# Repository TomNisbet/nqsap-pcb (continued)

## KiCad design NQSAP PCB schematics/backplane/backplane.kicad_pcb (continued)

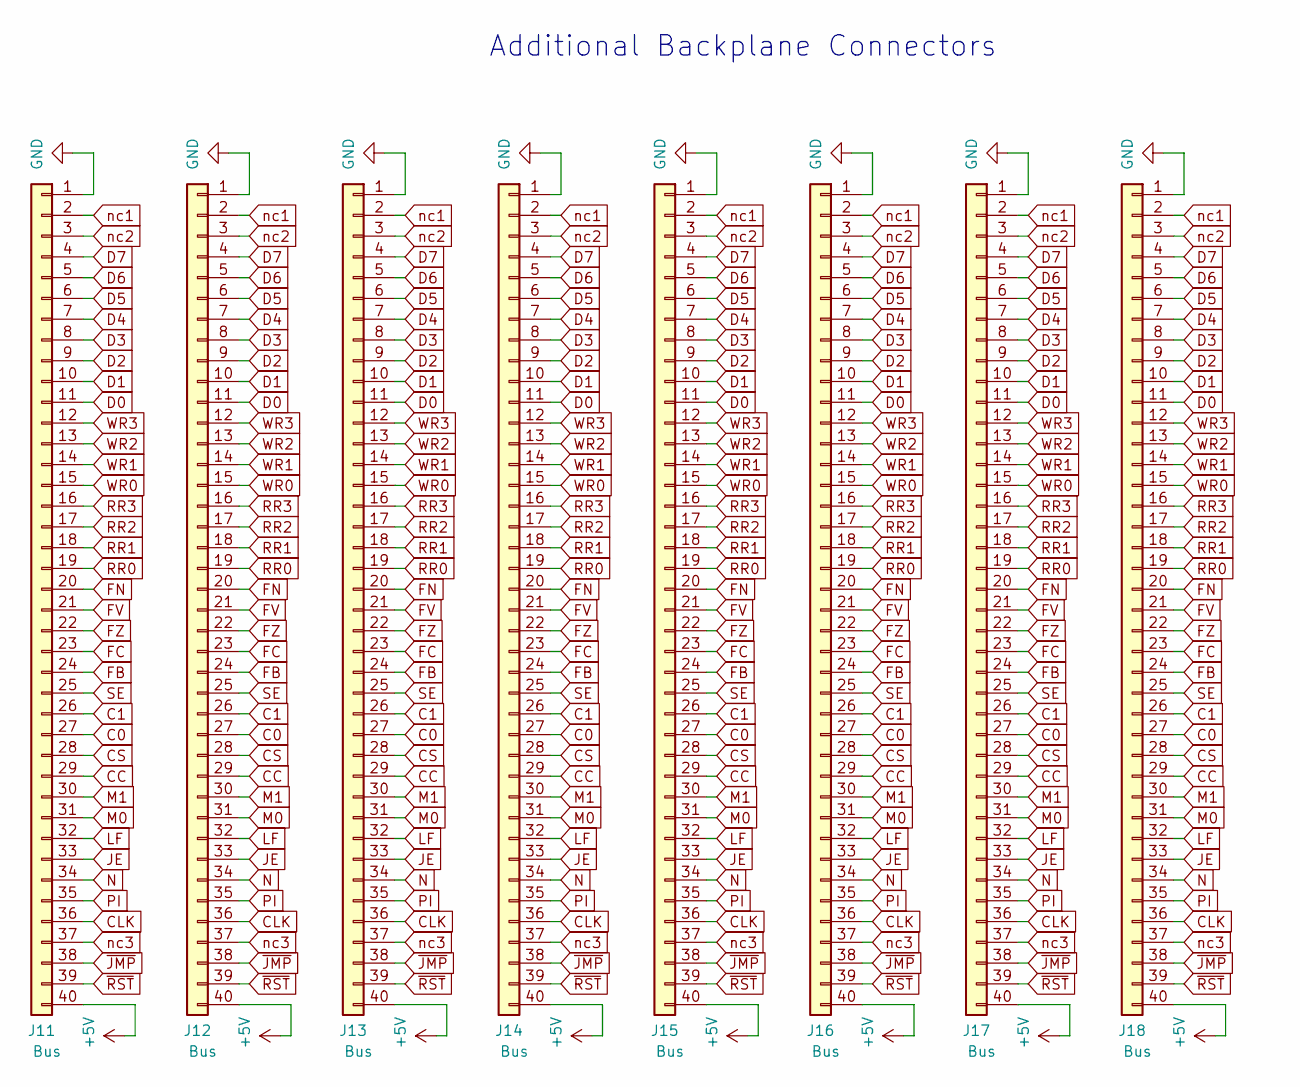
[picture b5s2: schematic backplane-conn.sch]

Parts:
J11, J12, J13, J14, J15, J16, J17, J18: Bus; PinSocket_1x40_P2.54mm_Vertical

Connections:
+5V: J11.40, J12.40, J13.40, J14.40, J15.40, J16.40, J17.40, J18.40; also elsewhere on the board
C0: J11.27, J12.27, J13.27, J14.27, J15.27, J16.27, J17.27, J18.27; also elsewhere on the board
C1: J11.26, J12.26, J13.26, J14.26, J15.26, J16.26, J17.26, J18.26; also elsewhere on the board
CC: J11.29, J12.29, J13.29, J14.29, J15.29, J16.29, J17.29, J18.29; also elsewhere on the board
CLK: J11.36, J12.36, J13.36, J14.36, J15.36, J16.36, J17.36, J18.36; also elsewhere on the board
CS: J11.28, J12.28, J13.28, J14.28, J15.28, J16.28, J17.28, J18.28; also elsewhere on the board
D0: J11.11, J12.11, J13.11, J14.11, J15.11, J16.11, J17.11, J18.11; also elsewhere on the board
D1: J11.10, J12.10, J13.10, J14.10, J15.10, J16.10, J17.10, J18.10; also elsewhere on the board
D2: J11.9, J12.9, J13.9, J14.9, J15.9, J16.9, J17.9, J18.9; also elsewhere on the board
D3: J11.8, J12.8, J13.8, J14.8, J15.8, J16.8, J17.8, J18.8; also elsewhere on the board
D4: J11.7, J12.7, J13.7, J14.7, J15.7, J16.7, J17.7, J18.7; also elsewhere on the board
D5: J11.6, J12.6, J13.6, J14.6, J15.6, J16.6, J17.6, J18.6; also elsewhere on the board
D6: J11.5, J12.5, J13.5, J14.5, J15.5, J16.5, J17.5, J18.5; also elsewhere on the board
D7: J11.4, J12.4, J13.4, J14.4, J15.4, J16.4, J17.4, J18.4; also elsewhere on the board
FB: J11.24, J12.24, J13.24, J14.24, J15.24, J16.24, J17.24, J18.24; also elsewhere on the board
FC: J11.23, J12.23, J13.23, J14.23, J15.23, J16.23, J17.23, J18.23; also elsewhere on the board
FN: J11.20, J12.20, J13.20, J14.20, J15.20, J16.20, J17.20, J18.20; also elsewhere on the board
FV: J11.21, J12.21, J13.21, J14.21, J15.21, J16.21, J17.21, J18.21; also elsewhere on the board
FZ: J11.22, J12.22, J13.22, J14.22, J15.22, J16.22, J17.22, J18.22; also elsewhere on the board
GND: J11.1, J12.1, J13.1, J14.1, J15.1, J16.1, J17.1, J18.1; also elsewhere on the board
JE: J11.33, J12.33, J13.33, J14.33, J15.33, J16.33, J17.33, J18.33; also elsewhere on the board
LF: J11.32, J12.32, J13.32, J14.32, J15.32, J16.32, J17.32, J18.32; also elsewhere on the board
M0: J11.31, J12.31, J13.31, J14.31, J15.31, J16.31, J17.31, J18.31; also elsewhere on the board
M1: J11.30, J12.30, J13.30, J14.30, J15.30, J16.30, J17.30, J18.30; also elsewhere on the board
N: J11.34, J12.34, J13.34, J14.34, J15.34, J16.34, J17.34, J18.34; also elsewhere on the board
PI: J11.35, J12.35, J13.35, J14.35, J15.35, J16.35, J17.35, J18.35; also elsewhere on the board
RR0: J11.19, J12.19, J13.19, J14.19, J15.19, J16.19, J17.19, J18.19; also elsewhere on the board
RR1: J11.18, J12.18, J13.18, J14.18, J15.18, J16.18, J17.18, J18.18; also elsewhere on the board
RR2: J11.17, J12.17, J13.17, J14.17, J15.17, J16.17, J17.17, J18.17; also elsewhere on the board
RR3: J11.16, J12.16, J13.16, J14.16, J15.16, J16.16, J17.16, J18.16; also elsewhere on the board
SE: J11.25, J12.25, J13.25, J14.25, J15.25, J16.25, J17.25, J18.25; also elsewhere on the board
WR0: J11.15, J12.15, J13.15, J14.15, J15.15, J16.15, J17.15, J18.15; also elsewhere on the board
WR1: J11.14, J12.14, J13.14, J14.14, J15.14, J16.14, J17.14, J18.14; also elsewhere on the board
WR2: J11.13, J12.13, J13.13, J14.13, J15.13, J16.13, J17.13, J18.13; also elsewhere on the board
WR3: J11.12, J12.12, J13.12, J14.12, J15.12, J16.12, J17.12, J18.12; also elsewhere on the board
nc1: J11.2, J12.2, J13.2, J14.2, J15.2, J16.2, J17.2, J18.2; also elsewhere on the board
nc2: J11.3, J12.3, J13.3, J14.3, J15.3, J16.3, J17.3, J18.3; also elsewhere on the board
nc3: J11.37, J12.37, J13.37, J14.37, J15.37, J16.37, J17.37, J18.37; also elsewhere on the board
~JMP: J11.38, J12.38, J13.38, J14.38, J15.38, J16.38, J17.38, J18.38; also elsewhere on the board
~RST: J11.39, J12.39, J13.39, J14.39, J15.39, J16.39, J17.39, J18.39; also elsewhere on the board

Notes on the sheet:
Additional Backplane Connectors

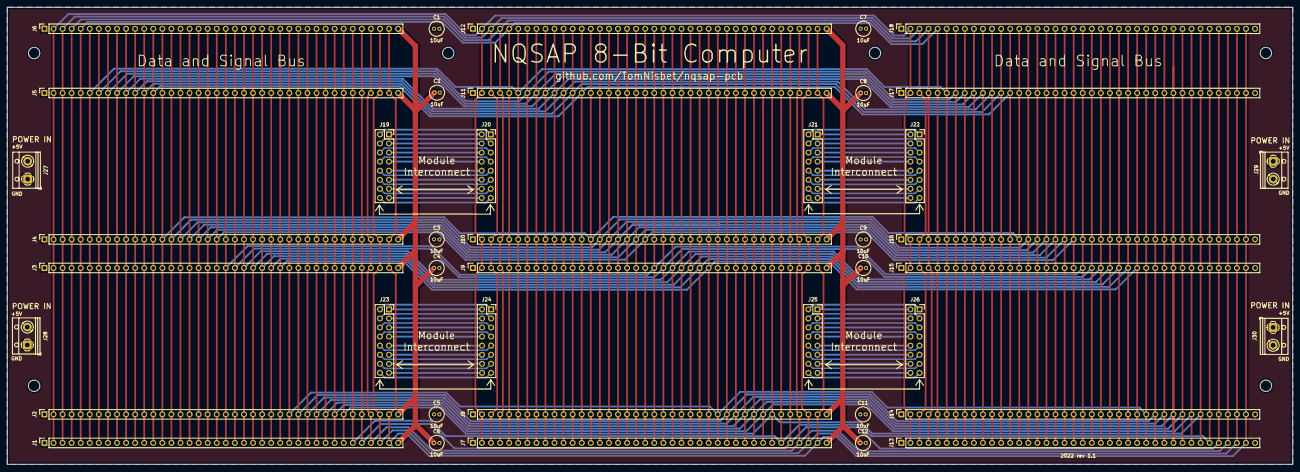
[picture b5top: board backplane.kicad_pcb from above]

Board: 2 copper layers, 360.0 x 128.0 mm, 42 parts (0 on the bottom side), 104 nets.

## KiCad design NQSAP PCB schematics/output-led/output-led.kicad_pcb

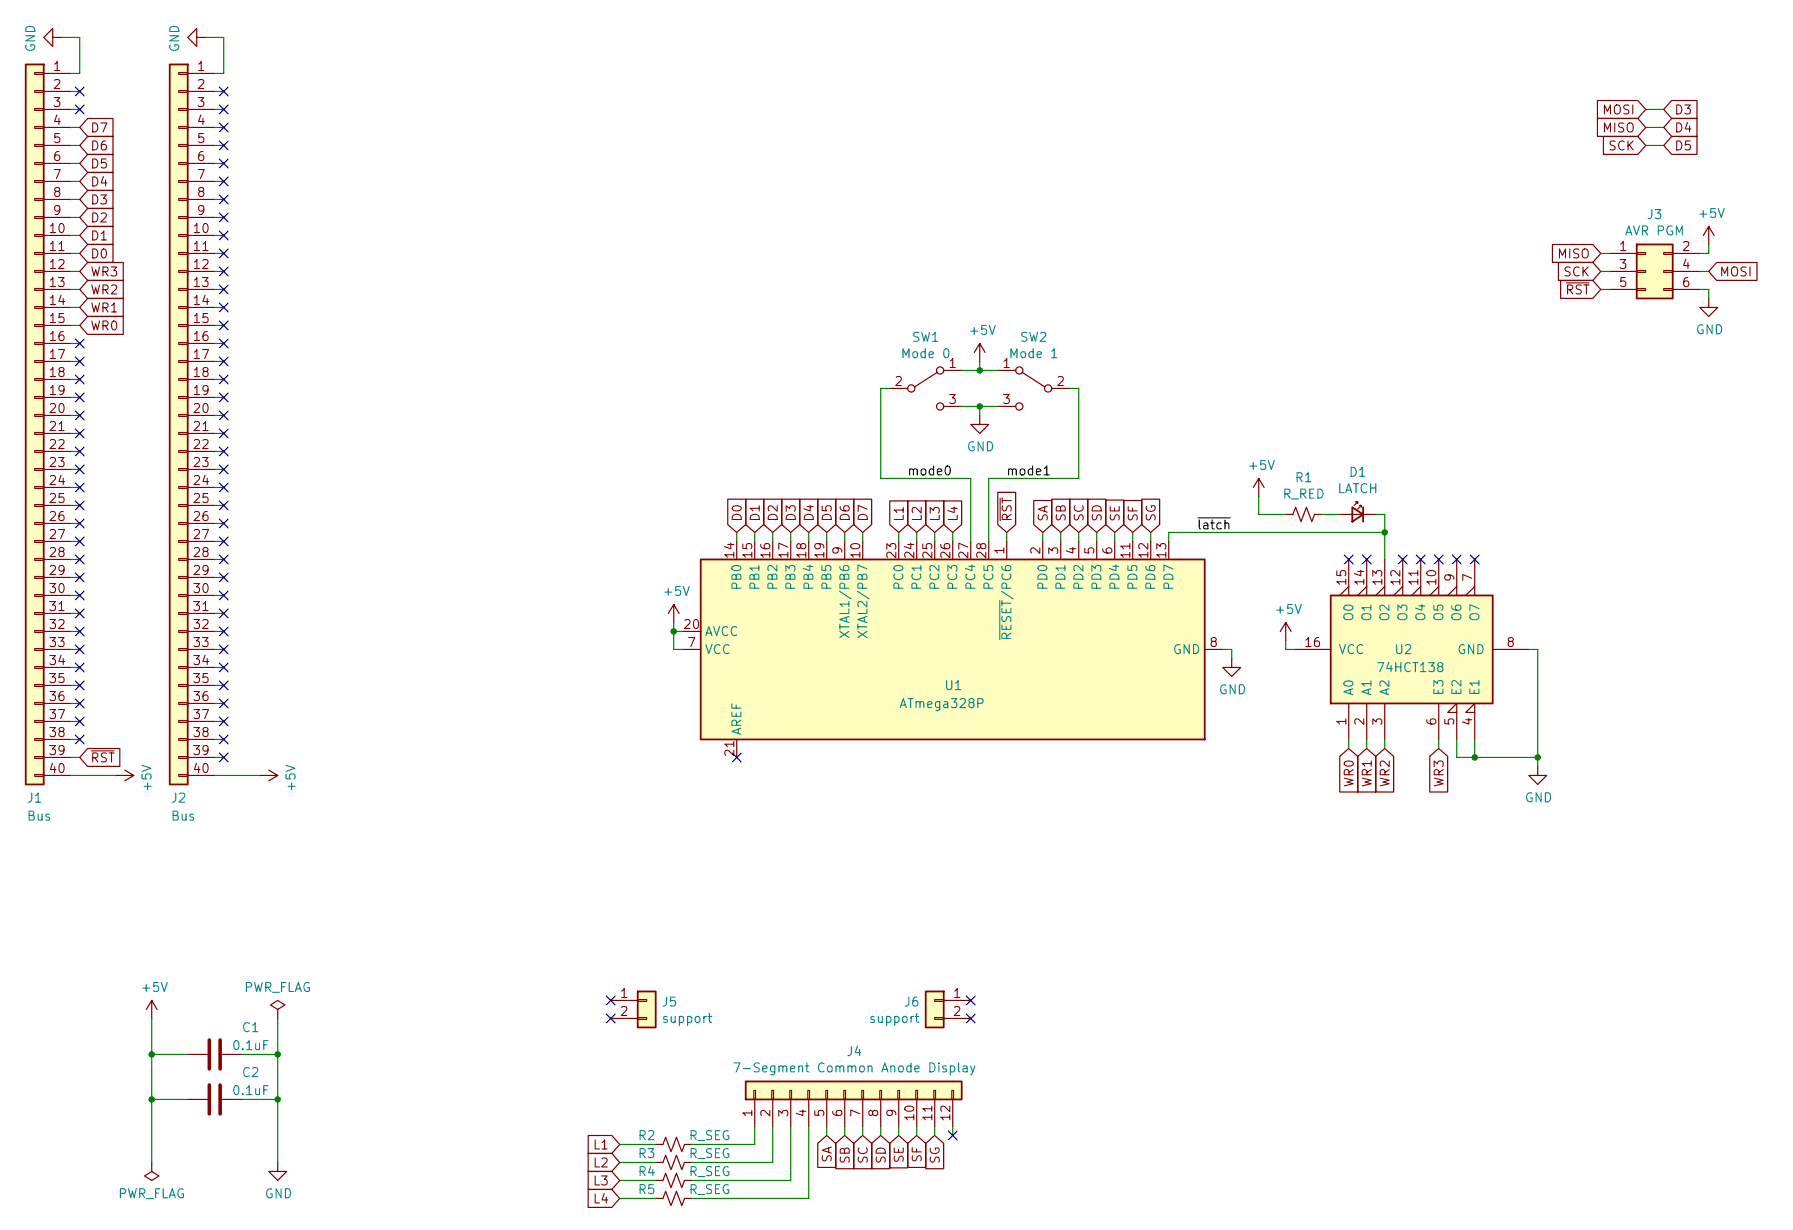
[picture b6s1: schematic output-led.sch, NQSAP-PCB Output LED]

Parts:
C1, C2: 0.1uF; C_0805_2012Metric_Pad1.18x1.45mm_HandSolder
D1: LATCH; LED_0805_2012Metric_Pad1.15x1.40mm_HandSolder
J1, J2: Bus; PinHeader_1x40_P2.54mm_Vertical
J3: AVR PGM; PinHeader_2x03_P2.54mm_Vertical
J4: 7-Segment Common Anode Display; PinSocket_1x12_P2.54mm_Vertical
J5, J6: support; PinSocket_1x02_P2.54mm_Vertical
R1: R_RED; R_0805_2012Metric_Pad1.20x1.40mm_HandSolder
R2, R3, R4, R5: R_SEG; R_0805_2012Metric_Pad1.20x1.40mm_HandSolder
SW1: Mode 0; Switch_Slide_11.6x4mm_EG1218
SW2: Mode 1; Switch_Slide_11.6x4mm_EG1218
U1: ATmega328P; DIP-28_W7.62mm
U2: 74HCT138; DIP-16_W7.62mm

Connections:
+5V: C1.2, C2.2, J1.40, J2.40, J3.2, R1.2, SW1.1 (A), SW2.1 (A), U1.7 (VCC), U1.20 (AVCC), U2.16 (VCC)
/mode0: SW1.2 (B), U1.27 (PC4)
/mode1: SW2.2 (B), U1.28 (PC5)
/~latch: D1.1 (K), U1.13 (PD7), U2.13 (O2)
D0: J1.11, U1.14 (PB0)
D1: J1.10, U1.15 (PB1)
D2: J1.9, U1.16 (PB2)
D3: J1.8, J3.4, U1.17 (PB3)
D4: J1.7, J3.1, U1.18 (PB4)
D5: J1.6, J3.3, U1.19 (PB5)
D6: J1.5, U1.9 (XTAL1/PB6)
D7: J1.4, U1.10 (XTAL2/PB7)
GND: C1.1, C2.1, J1.1, J2.1, J3.6, SW1.3 (C), SW2.3 (C), U1.8 (GND), U1.22 (GND), U2.4 (E1), U2.5 (E2), U2.8 (GND)
L1: R2.2, U1.23 (PC0)
L2: R3.2, U1.24 (PC1)
L3: R4.2, U1.25 (PC2)
L4: R5.2, U1.26 (PC3)
unnamed: D1.2 (A), R1.1
unnamed: J4.1, R2.1
unnamed: J4.2, R3.1
unnamed: J4.3, R4.1
unnamed: J4.4, R5.1
SA: J4.5, U1.2 (PD0)
SB: J4.6, U1.3 (PD1)
SC: J4.7, U1.4 (PD2)
SD: J4.8, U1.5 (PD3)
SE: J4.9, U1.6 (PD4)
SF: J4.10, U1.11 (PD5)
SG: J4.11, U1.12 (PD6)
WR0: J1.15, U2.1 (A0)
WR1: J1.14, U2.2 (A1)
WR2: J1.13, U2.3 (A2)
WR3: J1.12, U2.6 (E3)
~RST: J1.39, J3.5, U1.1 (~RESET~/PC6)

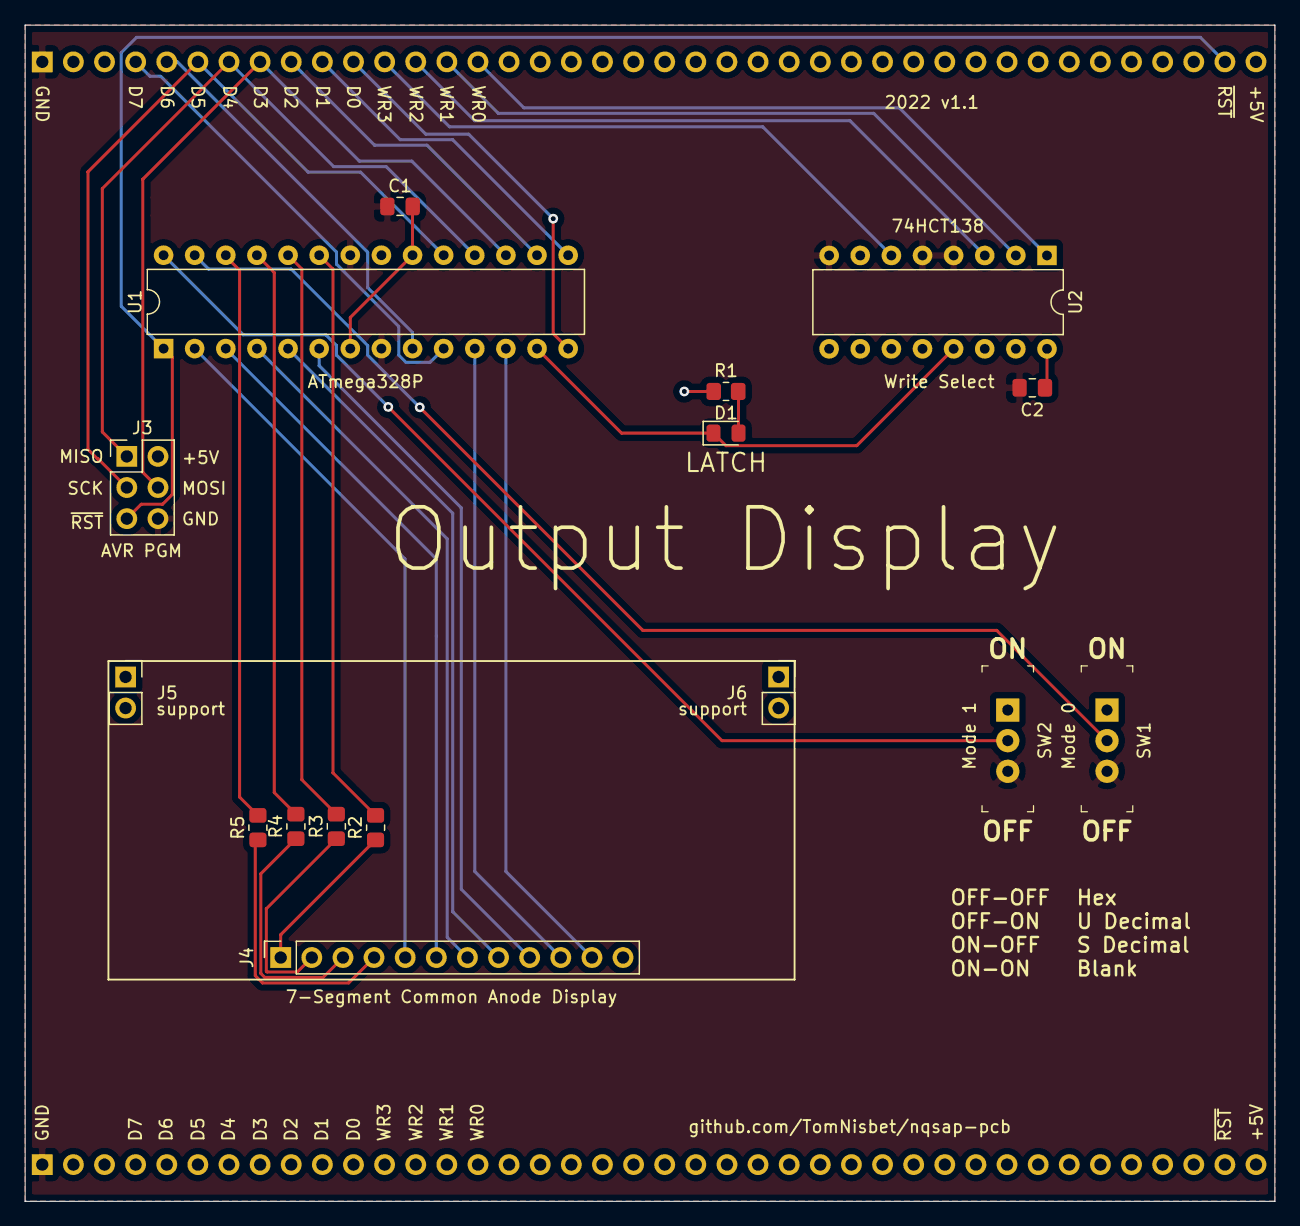
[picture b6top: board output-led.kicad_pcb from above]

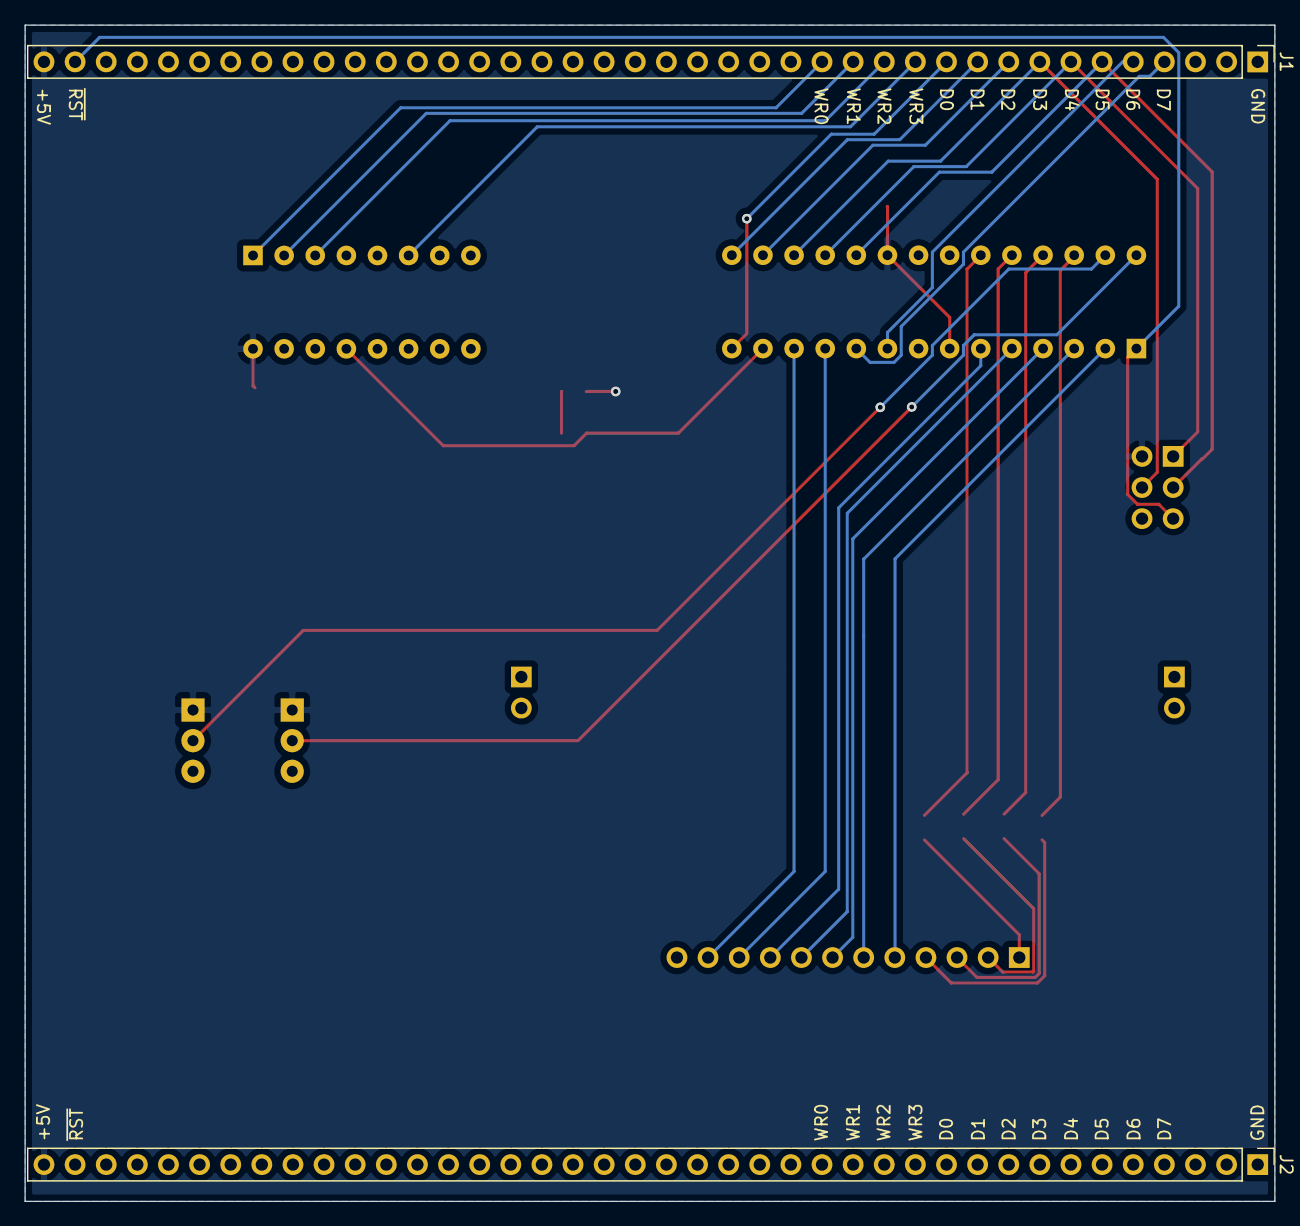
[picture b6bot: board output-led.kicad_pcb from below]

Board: 2 copper layers, 102.0 x 96.0 mm, 18 parts (2 on the bottom side), 34 nets.

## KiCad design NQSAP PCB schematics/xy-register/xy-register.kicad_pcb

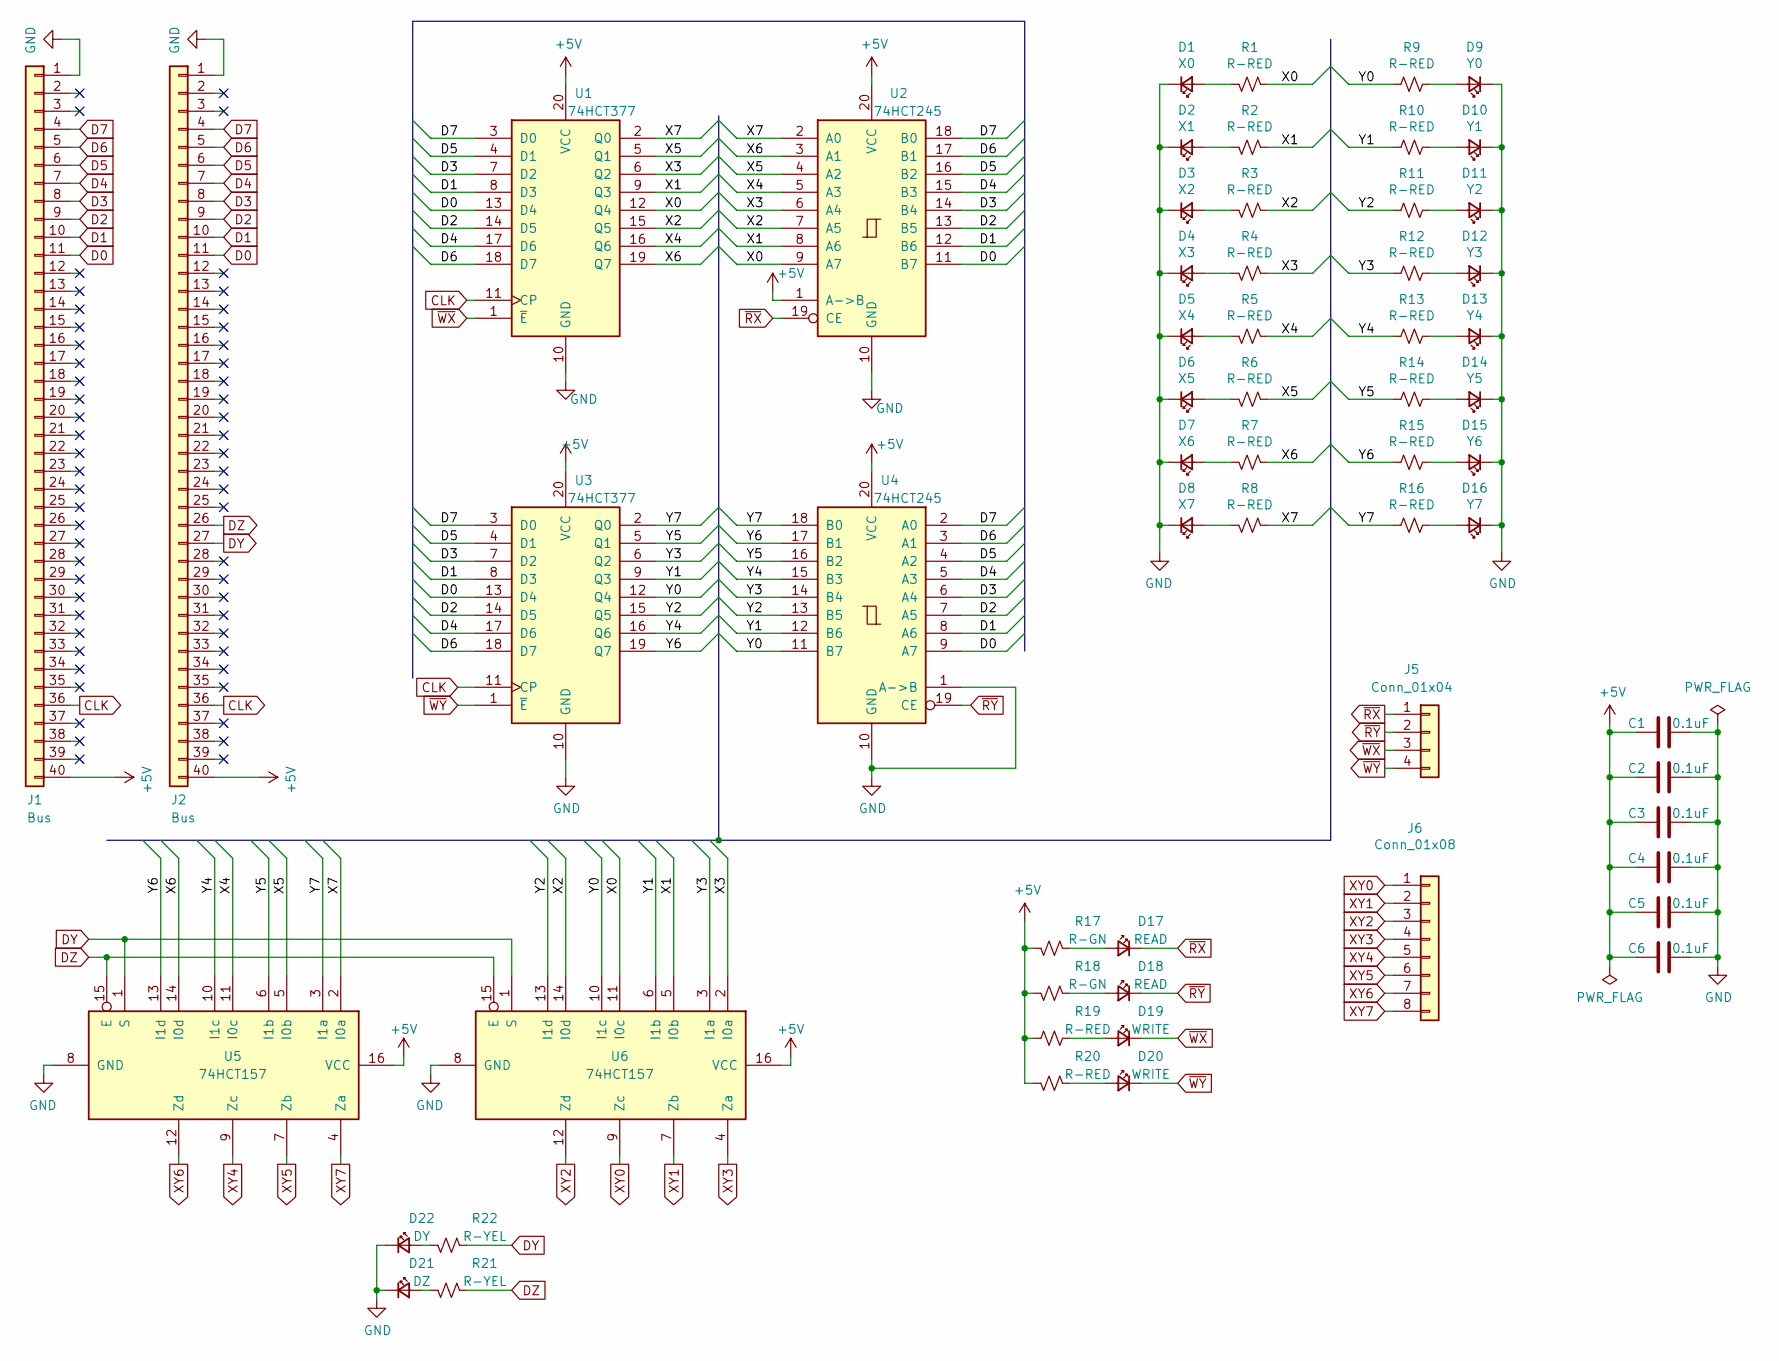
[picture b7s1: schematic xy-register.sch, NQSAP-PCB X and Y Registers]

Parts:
C1, C2, C3, C4, C5, C6: 0.1uF; C_0805_2012Metric_Pad1.18x1.45mm_HandSolder
D1: X0; LED_0805_2012Metric_Pad1.15x1.40mm_HandSolder
D2: X1; LED_0805_2012Metric_Pad1.15x1.40mm_HandSolder
D3: X2; LED_0805_2012Metric_Pad1.15x1.40mm_HandSolder
D4: X3; LED_0805_2012Metric_Pad1.15x1.40mm_HandSolder
D5: X4; LED_0805_2012Metric_Pad1.15x1.40mm_HandSolder
D6: X5; LED_0805_2012Metric_Pad1.15x1.40mm_HandSolder
D7: X6; LED_0805_2012Metric_Pad1.15x1.40mm_HandSolder
D8: X7; LED_0805_2012Metric_Pad1.15x1.40mm_HandSolder
D9: Y0; LED_0805_2012Metric_Pad1.15x1.40mm_HandSolder
D10: Y1; LED_0805_2012Metric_Pad1.15x1.40mm_HandSolder
D11: Y2; LED_0805_2012Metric_Pad1.15x1.40mm_HandSolder
D12: Y3; LED_0805_2012Metric_Pad1.15x1.40mm_HandSolder
D13: Y4; LED_0805_2012Metric_Pad1.15x1.40mm_HandSolder
D14: Y5; LED_0805_2012Metric_Pad1.15x1.40mm_HandSolder
D15: Y6; LED_0805_2012Metric_Pad1.15x1.40mm_HandSolder
D16: Y7; LED_0805_2012Metric_Pad1.15x1.40mm_HandSolder
D17, D18: READ; LED_0805_2012Metric_Pad1.15x1.40mm_HandSolder
D19, D20: WRITE; LED_0805_2012Metric_Pad1.15x1.40mm_HandSolder
D21: DZ; LED_0805_2012Metric_Pad1.15x1.40mm_HandSolder
D22: DY; LED_0805_2012Metric_Pad1.15x1.40mm_HandSolder
J1, J2: Bus; PinHeader_1x40_P2.54mm_Vertical
J5: Conn_01x04; PinHeader_1x04_P2.54mm_Vertical
J6: Conn_01x08; PinHeader_1x08_P2.54mm_Vertical
R1, R2, R3, R4, R5, R6, R7, R8, R9, R10, R11, R12, R13, R14, R15, R16, R19, R20: R-RED; R_0805_2012Metric_Pad1.20x1.40mm_HandSolder
R17, R18: R-GN; R_0805_2012Metric_Pad1.20x1.40mm_HandSolder
R21, R22: R-YEL; R_0805_2012Metric_Pad1.20x1.40mm_HandSolder
U1, U3: 74HCT377; DIP-20_W7.62mm
U2, U4: 74HCT245; DIP-20_W7.62mm
U5, U6: 74HCT157; DIP-16_W7.62mm

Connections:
+5V: C1.2, C2.2, C3.2, C4.2, C5.2, C6.2, J1.40, J2.40, R17.1, R18.1, R19.2, R20.1, U1.20 (VCC), U2.1 (A->B), U2.20 (VCC), U3.20 (VCC), U4.20 (VCC), U5.16 (VCC), U6.16 (VCC)
/X0: R1.2, U1.12 (Q4), U2.9 (A7), U6.11 (I0c)
/X1: R2.2, U1.9 (Q3), U2.8 (A6), U6.5 (I0b)
/X2: R3.2, U1.15 (Q5), U2.7 (A5), U6.14 (I0d)
/X3: R4.2, U1.6 (Q2), U2.6 (A4), U6.2 (I0a)
/X4: R5.2, U1.16 (Q6), U2.5 (A3), U5.11 (I0c)
/X5: R6.2, U1.5 (Q1), U2.4 (A2), U5.5 (I0b)
/X6: R7.2, U1.19 (Q7), U2.3 (A1), U5.14 (I0d)
/X7: R8.2, U1.2 (Q0), U2.2 (A0), U5.2 (I0a)
/Y0: R9.2, U3.12 (Q4), U4.11 (B7), U6.10 (I1c)
/Y1: R10.2, U3.9 (Q3), U4.12 (B6), U6.6 (I1b)
/Y2: R11.2, U3.15 (Q5), U4.13 (B5), U6.13 (I1d)
/Y3: R12.2, U3.6 (Q2), U4.14 (B4), U6.3 (I1a)
/Y4: R13.2, U3.16 (Q6), U4.15 (B3), U5.10 (I1c)
/Y5: R14.2, U3.5 (Q1), U4.16 (B2), U5.6 (I1b)
/Y6: R15.2, U3.19 (Q7), U4.17 (B1), U5.13 (I1d)
/Y7: R16.2, U3.2 (Q0), U4.18 (B0), U5.3 (I1a)
CLK: J1.36, J2.36, U1.11 (CP), U3.11 (CP)
D0: J1.11, J2.11, U1.13 (D4), U2.11 (B7), U3.13 (D4), U4.9 (A7)
D1: J1.10, J2.10, U1.8 (D3), U2.12 (B6), U3.8 (D3), U4.8 (A6)
D2: J1.9, J2.9, U1.14 (D5), U2.13 (B5), U3.14 (D5), U4.7 (A5)
D3: J1.8, J2.8, U1.7 (D2), U2.14 (B4), U3.7 (D2), U4.6 (A4)
D4: J1.7, J2.7, U1.17 (D6), U2.15 (B3), U3.17 (D6), U4.5 (A3)
D5: J1.6, J2.6, U1.4 (D1), U2.16 (B2), U3.4 (D1), U4.4 (A2)
D6: J1.5, J2.5, U1.18 (D7), U2.17 (B1), U3.18 (D7), U4.3 (A1)
D7: J1.4, J2.4, U1.3 (D0), U2.18 (B0), U3.3 (D0), U4.2 (A0)
DY: J2.27, R22.2, U5.1 (S), U6.1 (S)
DZ: J2.26, R21.2, U5.15 (E), U6.15 (E)
GND: C1.1, C2.1, C3.1, C4.1, C5.1, C6.1, D1.1 (K), D2.1 (K), D3.1 (K), D4.1 (K), D5.1 (K), D6.1 (K), D7.1 (K), D8.1 (K), D9.1 (K), D10.1 (K), D11.1 (K), D12.1 (K), D13.1 (K), D14.1 (K), D15.1 (K), D16.1 (K), D21.1 (K), D22.1 (K), J1.1, J2.1, U1.10 (GND), U2.10 (GND), U3.10 (GND), U4.1 (A->B), U4.10 (GND), U5.8 (GND), U6.8 (GND)
unnamed: D1.2 (A), R1.1
unnamed: D2.2 (A), R2.1
unnamed: D3.2 (A), R3.1
unnamed: D4.2 (A), R4.1
unnamed: D5.2 (A), R5.1
unnamed: D6.2 (A), R6.1
unnamed: D7.2 (A), R7.1
unnamed: D8.2 (A), R8.1
unnamed: D9.2 (A), R9.1
unnamed: D10.2 (A), R10.1
unnamed: D11.2 (A), R11.1
unnamed: D12.2 (A), R12.1
unnamed: D13.2 (A), R13.1
unnamed: D14.2 (A), R14.1
unnamed: D15.2 (A), R15.1
unnamed: D16.2 (A), R16.1
unnamed: D17.2 (A), R17.2
unnamed: D18.2 (A), R18.2
unnamed: D19.2 (A), R19.1
unnamed: D20.2 (A), R20.2
unnamed: D21.2 (A), R21.1
unnamed: D22.2 (A), R22.1
XY0: J6.1, U6.9 (Zc)
XY1: J6.2, U6.7 (Zb)
XY2: J6.3, U6.12 (Zd)
XY3: J6.4, U6.4 (Za)
XY4: J6.5, U5.9 (Zc)
XY5: J6.6, U5.7 (Zb)
XY6: J6.7, U5.12 (Zd)
XY7: J6.8, U5.4 (Za)
~RX: D17.1 (K), J5.1, U2.19 (CE)
~RY: D18.1 (K), J5.2, U4.19 (CE)
~WX: D19.1 (K), J5.3, U1.1 (~E)
~WY: D20.1 (K), J5.4, U3.1 (~E)

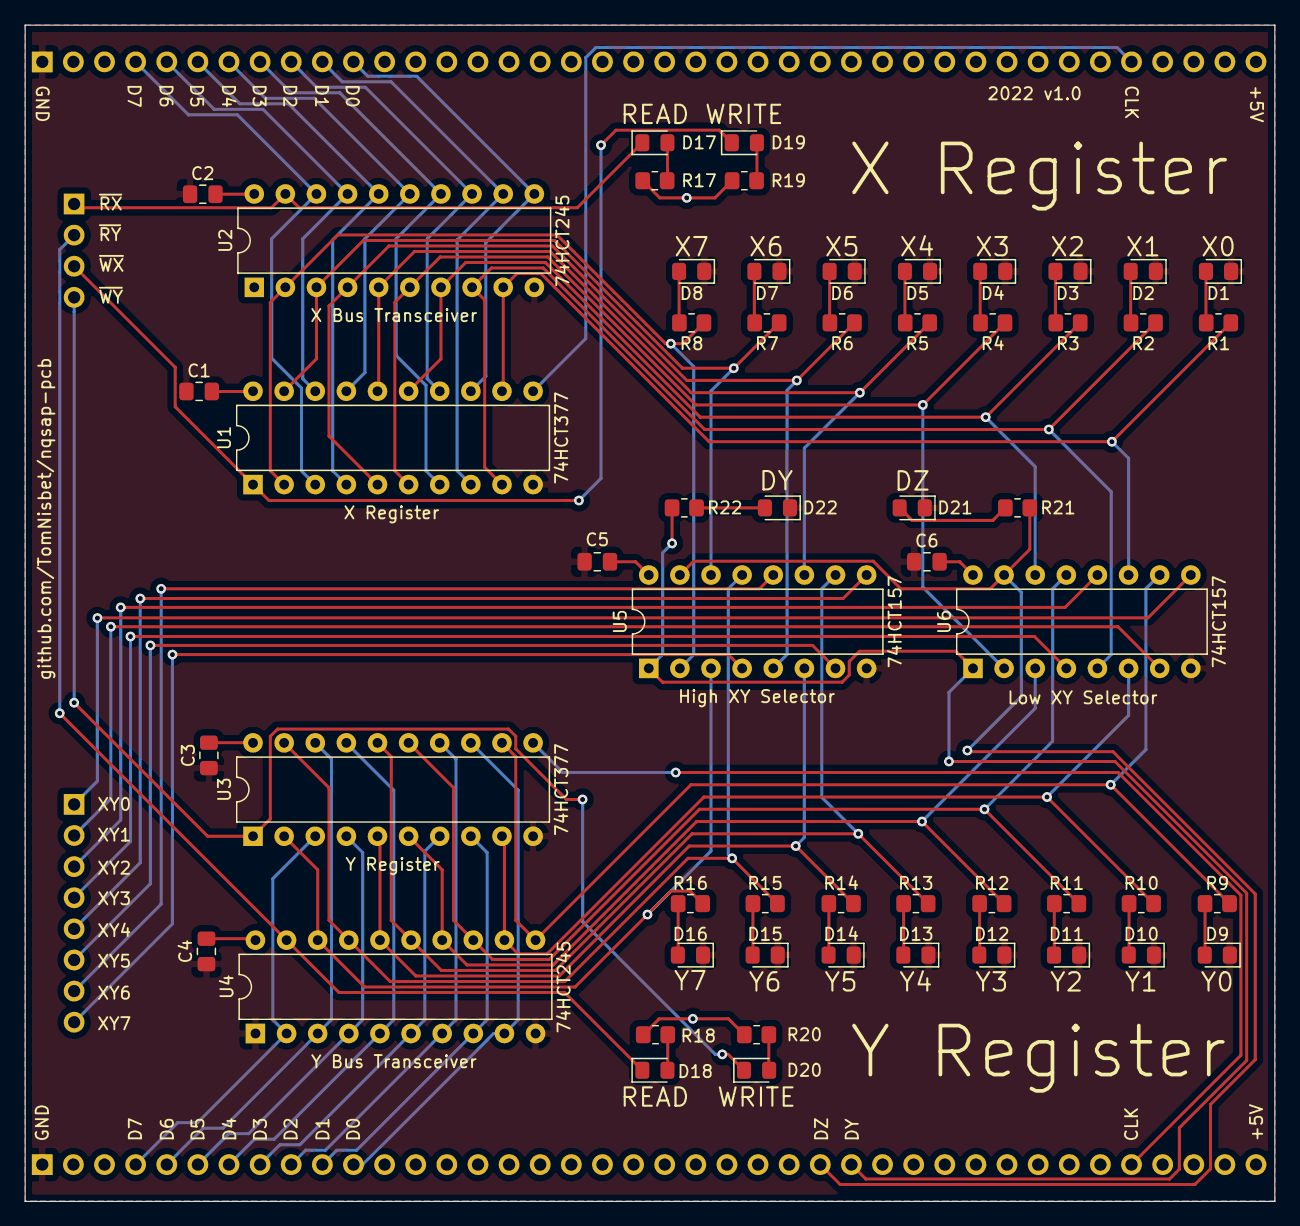
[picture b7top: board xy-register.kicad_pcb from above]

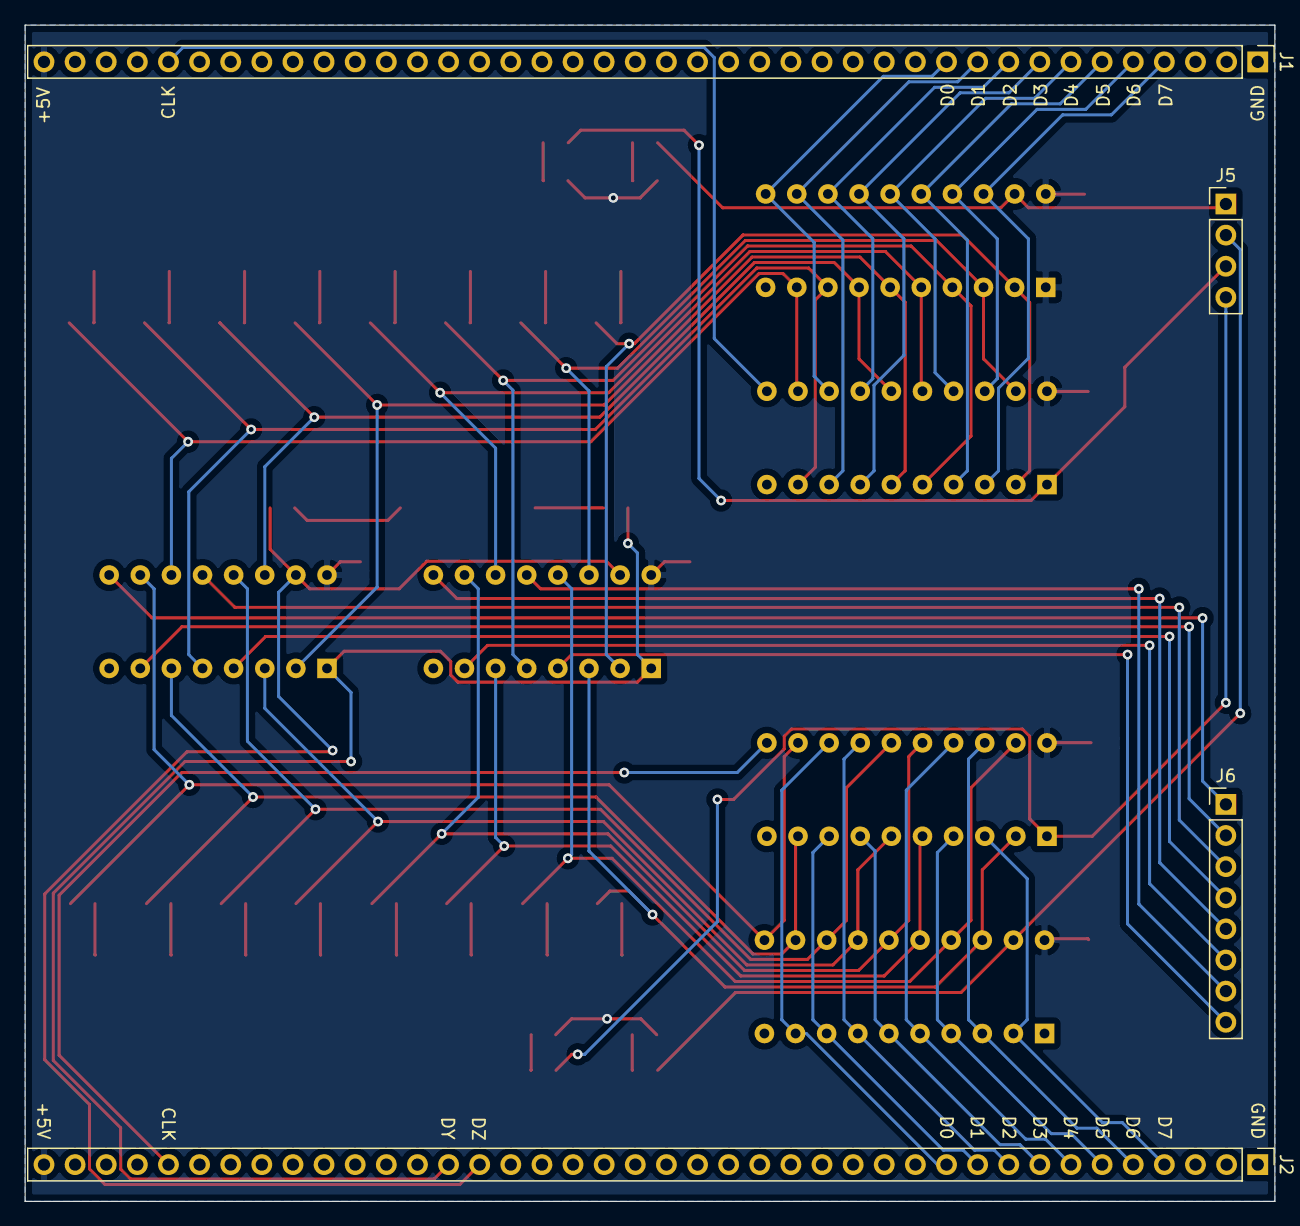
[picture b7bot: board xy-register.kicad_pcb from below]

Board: 2 copper layers, 102.0 x 96.0 mm, 60 parts (4 on the bottom side), 63 nets.
